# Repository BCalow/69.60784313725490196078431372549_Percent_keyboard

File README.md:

# 69.60784313725490196078431372549_Percent_keyboard
 custom keyboard project

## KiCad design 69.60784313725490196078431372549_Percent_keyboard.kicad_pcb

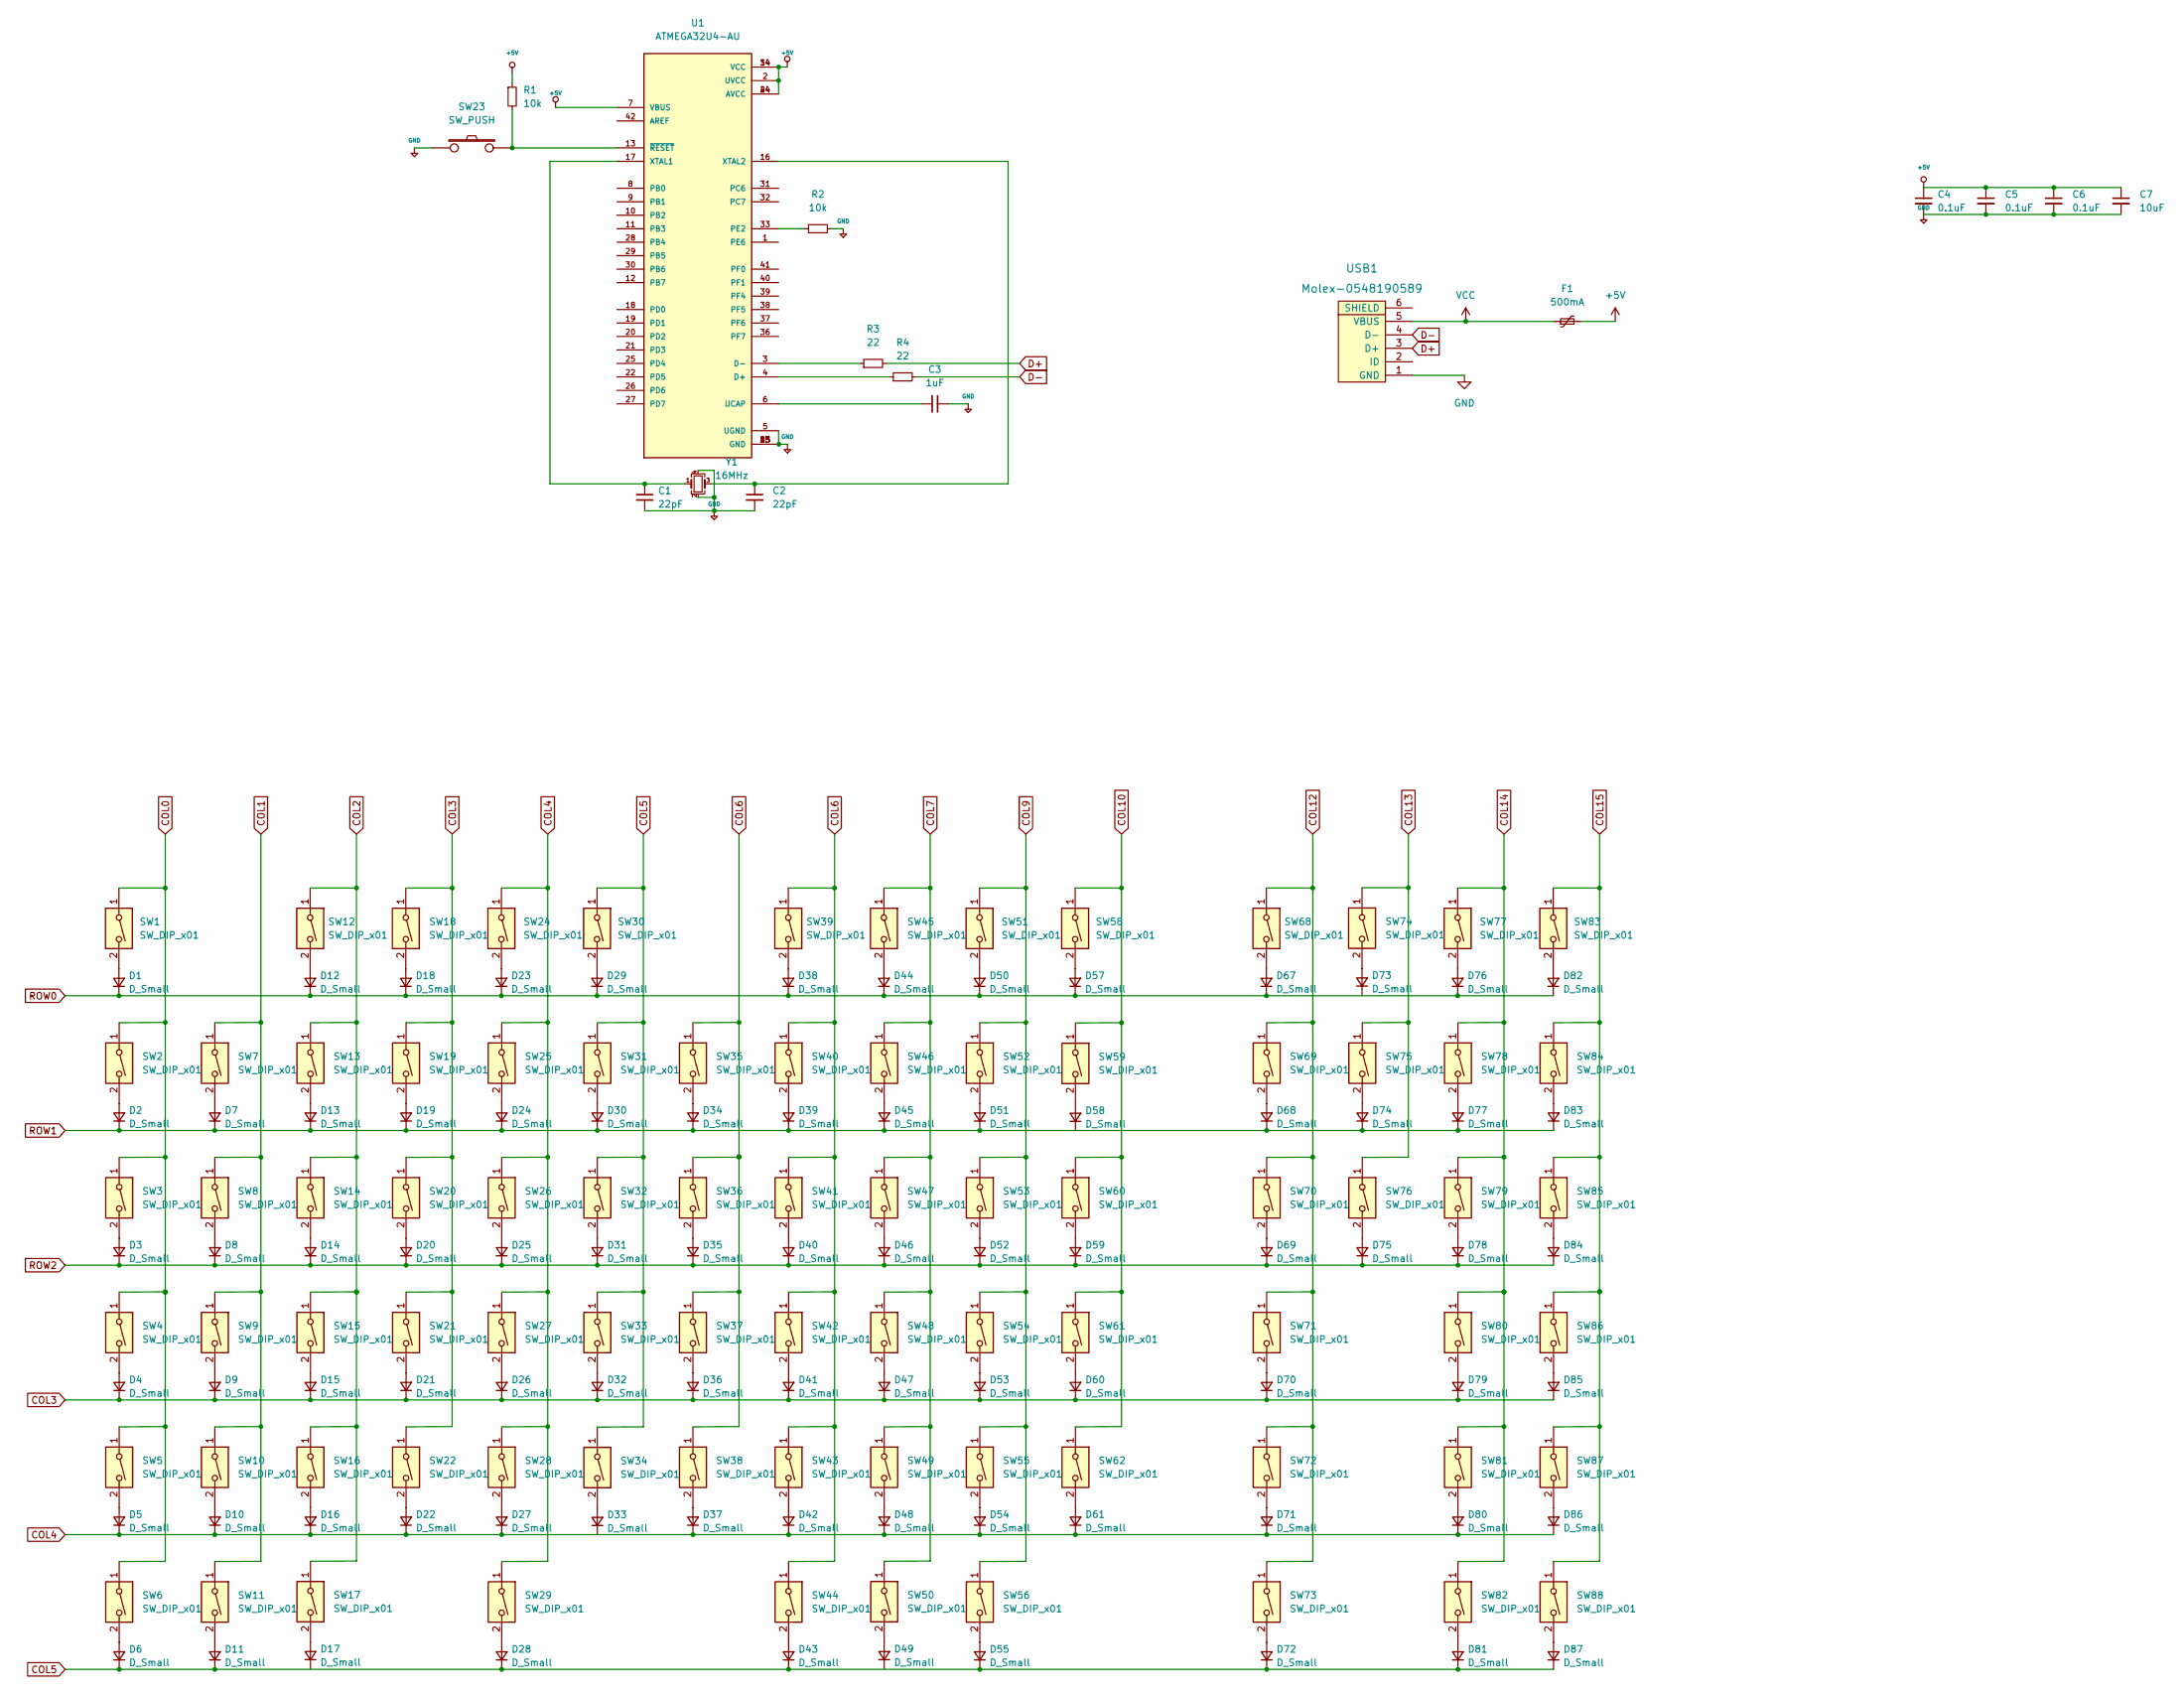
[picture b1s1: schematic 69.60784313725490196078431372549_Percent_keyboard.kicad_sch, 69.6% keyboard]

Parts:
C1, C2: 22pF; C_0805_2012Metric
C3: 1uF; C_0805_2012Metric
C4, C5, C6: 0.1uF; C_0805_2012Metric
C7: 10uF; C_0805_2012Metric
D1, D2, D3, D4, D5, D6, D7, D8, D9, D10, D11, D12, D13, D14, D15, D16, D17, D18, D19, D20, D21, D22, D23, D24, D25, D26, D27, D28, D29, D30, D31, D32, D33, D34, D35, D36, D37, D38, D39, D40, D41, D42, D43, D44, D45, D46, D47, D48, D49, D50, D51, D52, D53, D54, D55, D57, D58, D59, D60, D61, D67, D68, D69, D70, D71, D72, D73, D74, D75, D76, D77, D78, D79, D80, D81, D82, D83, D84, D85, D86, D87: D_Small; D_SOD-123
F1: 500mA; Fuse_1206_3216Metric
R1, R2: 10k; R_0805_2012Metric
R3, R4: 22; R_0805_2012Metric
SW1, SW2, SW7, SW8, SW9, SW10, SW12, SW13, SW14, SW15, SW16, SW18, SW19, SW20, SW21, SW22, SW24, SW25, SW26, SW27, SW28, SW30, SW31, SW32, SW33, SW34, SW35, SW36, SW37, SW38, SW39, SW40, SW41, SW42, SW43, SW45, SW46, SW47, SW48, SW49, SW51, SW52, SW53, SW54, SW55, SW58, SW59, SW60, SW61, SW62, SW68, SW69, SW70, SW71, SW74, SW75, SW76, SW77, SW81, SW83, SW84, SW85, SW86, SW87, SW88: SW_DIP_x01; CherryMX_1.00u_KailhSocket_LED
SW3, SW79: SW_DIP_x01; CherryMX_1.50u_KailhSocket_LED
SW4, SW73: SW_DIP_x01; CherryMX_1.75u_KailhSocket_LED
SW5, SW72, SW78: SW_DIP_x01; CherryMX_2.00u_KailhSocket_LED
SW6, SW11, SW17, SW44, SW50, SW56, SW82: SW_DIP_x01; CherryMX_1.25u_KailhSocket_LED
SW23: SW_PUSH
SW29: SW_DIP_x01; CherryMX_6.00u_KailhSocket_LED
SW80: SW_DIP_x01; CherryMX_2.25u_KailhSocket_LED
U1: ATMEGA32U4-AU; QFP80P1200X1200X120-44N
USB1: Molex-0548190589
Y1: 16MHz; Fuse_1206_3216Metric

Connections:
COL0: SW1.1, SW2.1, SW3.1, SW4.1, SW5.1, SW6.1
COL1: SW7.1, SW8.1, SW9.1, SW10.1, SW11.1
COL2: SW12.1, SW13.1, SW14.1, SW15.1, SW16.1, SW17.1
COL3: D4.1 (K), D9.1 (K), D15.1 (K), D21.1 (K), D26.1 (K), D32.1 (K), D36.1 (K), D41.1 (K), D47.1 (K), D53.1 (K), D60.1 (K), D70.1 (K), D79.1 (K), D85.1 (K), SW18.1, SW19.1, SW20.1, SW21.1, SW22.1
COL4: D5.1 (K), D10.1 (K), D16.1 (K), D22.1 (K), D27.1 (K), D37.1 (K), D42.1 (K), D48.1 (K), D54.1 (K), D61.1 (K), D71.1 (K), D80.1 (K), D86.1 (K), SW24.1, SW25.1, SW26.1, SW27.1, SW28.1, SW29.1
COL5: D6.1 (K), D11.1 (K), D28.1 (K), D43.1 (K), D55.1 (K), D72.1 (K), D81.1 (K), D87.1 (K), SW30.1, SW31.1, SW32.1, SW33.1, SW34.1
COL6: SW35.1, SW36.1, SW37.1, SW38.1, SW39.1, SW40.1, SW41.1, SW42.1, SW43.1, SW44.1
COL7: SW45.1, SW46.1, SW47.1, SW48.1, SW49.1, SW50.1
COL9: SW51.1, SW52.1, SW53.1, SW54.1, SW55.1, SW56.1
COL10: SW58.1, SW59.1, SW60.1, SW61.1, SW62.1
COL12: SW68.1, SW69.1, SW70.1, SW71.1, SW72.1, SW73.1
COL13: SW74.1, SW75.1, SW76.1
COL14: SW77.1, SW78.1, SW79.1, SW80.1, SW81.1, SW82.1
COL15: SW83.1, SW84.1, SW85.1, SW86.1, SW87.1, SW88.1
D+: R3.2, USB1.3 (D+)
D-: R4.2, USB1.4 (D-)
unnamed: C1.1, U1.17 (XTAL1), Y1.1
unnamed: C2.1, U1.16 (XTAL2), Y1.3
unnamed: C3.1, U1.6 (UCAP)
unnamed: D1.2 (A), SW1.2
unnamed: D2.2 (A), SW2.2
unnamed: D3.2 (A), SW3.2
unnamed: D4.2 (A), SW4.2
unnamed: D5.2 (A), SW5.2
unnamed: D6.2 (A), SW6.2
unnamed: D7.2 (A), SW7.2
unnamed: D8.2 (A), SW8.2
unnamed: D9.2 (A), SW9.2
unnamed: D10.2 (A), SW10.2
unnamed: D11.2 (A), SW11.2
unnamed: D12.2 (A), SW12.2
unnamed: D13.2 (A), SW13.2
unnamed: D14.2 (A), SW14.2
unnamed: D15.2 (A), SW15.2
unnamed: D16.2 (A), SW16.2
unnamed: D17.2 (A), SW17.2
unnamed: D18.2 (A), SW18.2
unnamed: D19.2 (A), SW19.2
unnamed: D20.2 (A), SW20.2
unnamed: D21.2 (A), SW21.2
unnamed: D22.2 (A), SW22.2
unnamed: D23.2 (A), SW24.2
unnamed: D24.2 (A), SW25.2
unnamed: D25.2 (A), SW26.2
unnamed: D26.2 (A), SW27.2
unnamed: D27.2 (A), SW28.2
unnamed: D28.2 (A), SW29.2
unnamed: D29.2 (A), SW30.2
unnamed: D30.2 (A), SW31.2
unnamed: D31.2 (A), SW32.2
unnamed: D32.2 (A), SW33.2
unnamed: D33.2 (A), SW34.2
unnamed: D34.2 (A), SW35.2
unnamed: D35.2 (A), SW36.2
unnamed: D36.2 (A), SW37.2
unnamed: D37.2 (A), SW38.2
unnamed: D38.2 (A), SW39.2
unnamed: D39.2 (A), SW40.2
unnamed: D40.2 (A), SW41.2
unnamed: D41.2 (A), SW42.2
unnamed: D42.2 (A), SW43.2
unnamed: D43.2 (A), SW44.2
unnamed: D44.2 (A), SW45.2
unnamed: D45.2 (A), SW46.2
unnamed: D46.2 (A), SW47.2
unnamed: D47.2 (A), SW48.2
unnamed: D48.2 (A), SW49.2
unnamed: D49.2 (A), SW50.2
unnamed: D50.2 (A), SW51.2
unnamed: D51.2 (A), SW52.2
unnamed: D52.2 (A), SW53.2
unnamed: D53.2 (A), SW54.2
unnamed: D54.2 (A), SW55.2
unnamed: D55.2 (A), SW56.2
unnamed: D57.2 (A), SW58.2
unnamed: D58.2 (A), SW59.2
unnamed: D59.2 (A), SW60.2
unnamed: D60.2 (A), SW61.2
unnamed: D61.2 (A), SW62.2
unnamed: D67.2 (A), SW68.2
unnamed: D68.2 (A), SW69.2
unnamed: D69.2 (A), SW70.2
unnamed: D70.2 (A), SW71.2
unnamed: D71.2 (A), SW72.2
unnamed: D72.2 (A), SW73.2
unnamed: D73.2 (A), SW74.2
unnamed: D74.2 (A), SW75.2
unnamed: D75.2 (A), SW76.2
unnamed: D76.2 (A), SW77.2
unnamed: D77.2 (A), SW78.2
unnamed: D78.2 (A), SW79.2
unnamed: D79.2 (A), SW80.2
unnamed: D80.2 (A), SW81.2
unnamed: D81.2 (A), SW82.2
unnamed: D82.2 (A), SW83.2
unnamed: D83.2 (A), SW84.2
unnamed: D84.2 (A), SW85.2
unnamed: D85.2 (A), SW86.2
unnamed: D86.2 (A), SW87.2
unnamed: D87.2 (A), SW88.2
unnamed: R1.2, SW23.2, U1.13 (~RESET)
unnamed: R2.1, U1.33 (PE2)
unnamed: R3.1, U1.3 (D-)
unnamed: R4.1, U1.4 (D+)
unnamed: U1.5 (UGND), U1.15 (GND), U1.23 (GND), U1.35 (GND), U1.43 (GND)
ROW0: D1.1 (K), D12.1 (K), D18.1 (K), D23.1 (K), D29.1 (K), D38.1 (K), D44.1 (K), D50.1 (K), D57.1 (K), D67.1 (K), D76.1 (K), D82.1 (K)
ROW1: D2.1 (K), D7.1 (K), D13.1 (K), D19.1 (K), D24.1 (K), D30.1 (K), D34.1 (K), D39.1 (K), D45.1 (K), D51.1 (K), D68.1 (K), D74.1 (K), D77.1 (K), D83.1 (K)
ROW2: D3.1 (K), D8.1 (K), D14.1 (K), D20.1 (K), D25.1 (K), D31.1 (K), D35.1 (K), D40.1 (K), D46.1 (K), D52.1 (K), D59.1 (K), D69.1 (K), D75.1 (K), D78.1 (K), D84.1 (K)
VCC: F1.1, USB1.5 (VBUS)

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
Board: 2 copper layers, 176 parts (0 on the bottom side), 103 nets, no tracks yet.

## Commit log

2022-03-02 Initialize Project
2022-03-02 Added keyboard footprints
2022-03-02 add footprint libraries
    added footprint libraries to KiCAD
2022-03-03 restarted schematic
    restarted project 02-03-2022
2022-03-03 reset push button, crystal
2022-03-04 fixing random keyboard parts.pretty
2022-03-04 re added random keyboard parts
2022-03-04 Started switches, finished usb
2022-03-04 Finished switches
2022-03-04 started adding footprints
2022-03-05 add kicad libraries finished footprints started PCB
2022-03-09 add kicad libraries
2022-03-12 Recommit 12-03-2022
